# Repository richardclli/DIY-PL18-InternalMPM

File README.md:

# DIY-PL18-InternalMPM
An internal MPM (Multi-Protocol Module) for Flysky PL18 Mod

This internal module works with the modified version of Flysky PL18 that flashes with EdgeTX:

https://github.com/EdgeTX/edgetx/wiki/PL18-Hardware-Mod-for-Complete-EdgeTX-Support

For MPM firmware download, please visit the official page:

https://github.com/pascallanger/DIY-Multiprotocol-TX-Module

## Installation Procedures:
1. Add an antenna to the PL18

2. Solder the power control wire to PI.00 pin

3. Install the PCB and insert the power control pin, you may need to use a sticky tape to ensure the MPM PCB is fixed to the PL18 PCB properly.

Note:
The 100k pull up resistor for the power control pin is for testing purpose, it DO NOT NEED to be soldered as per the images shown.

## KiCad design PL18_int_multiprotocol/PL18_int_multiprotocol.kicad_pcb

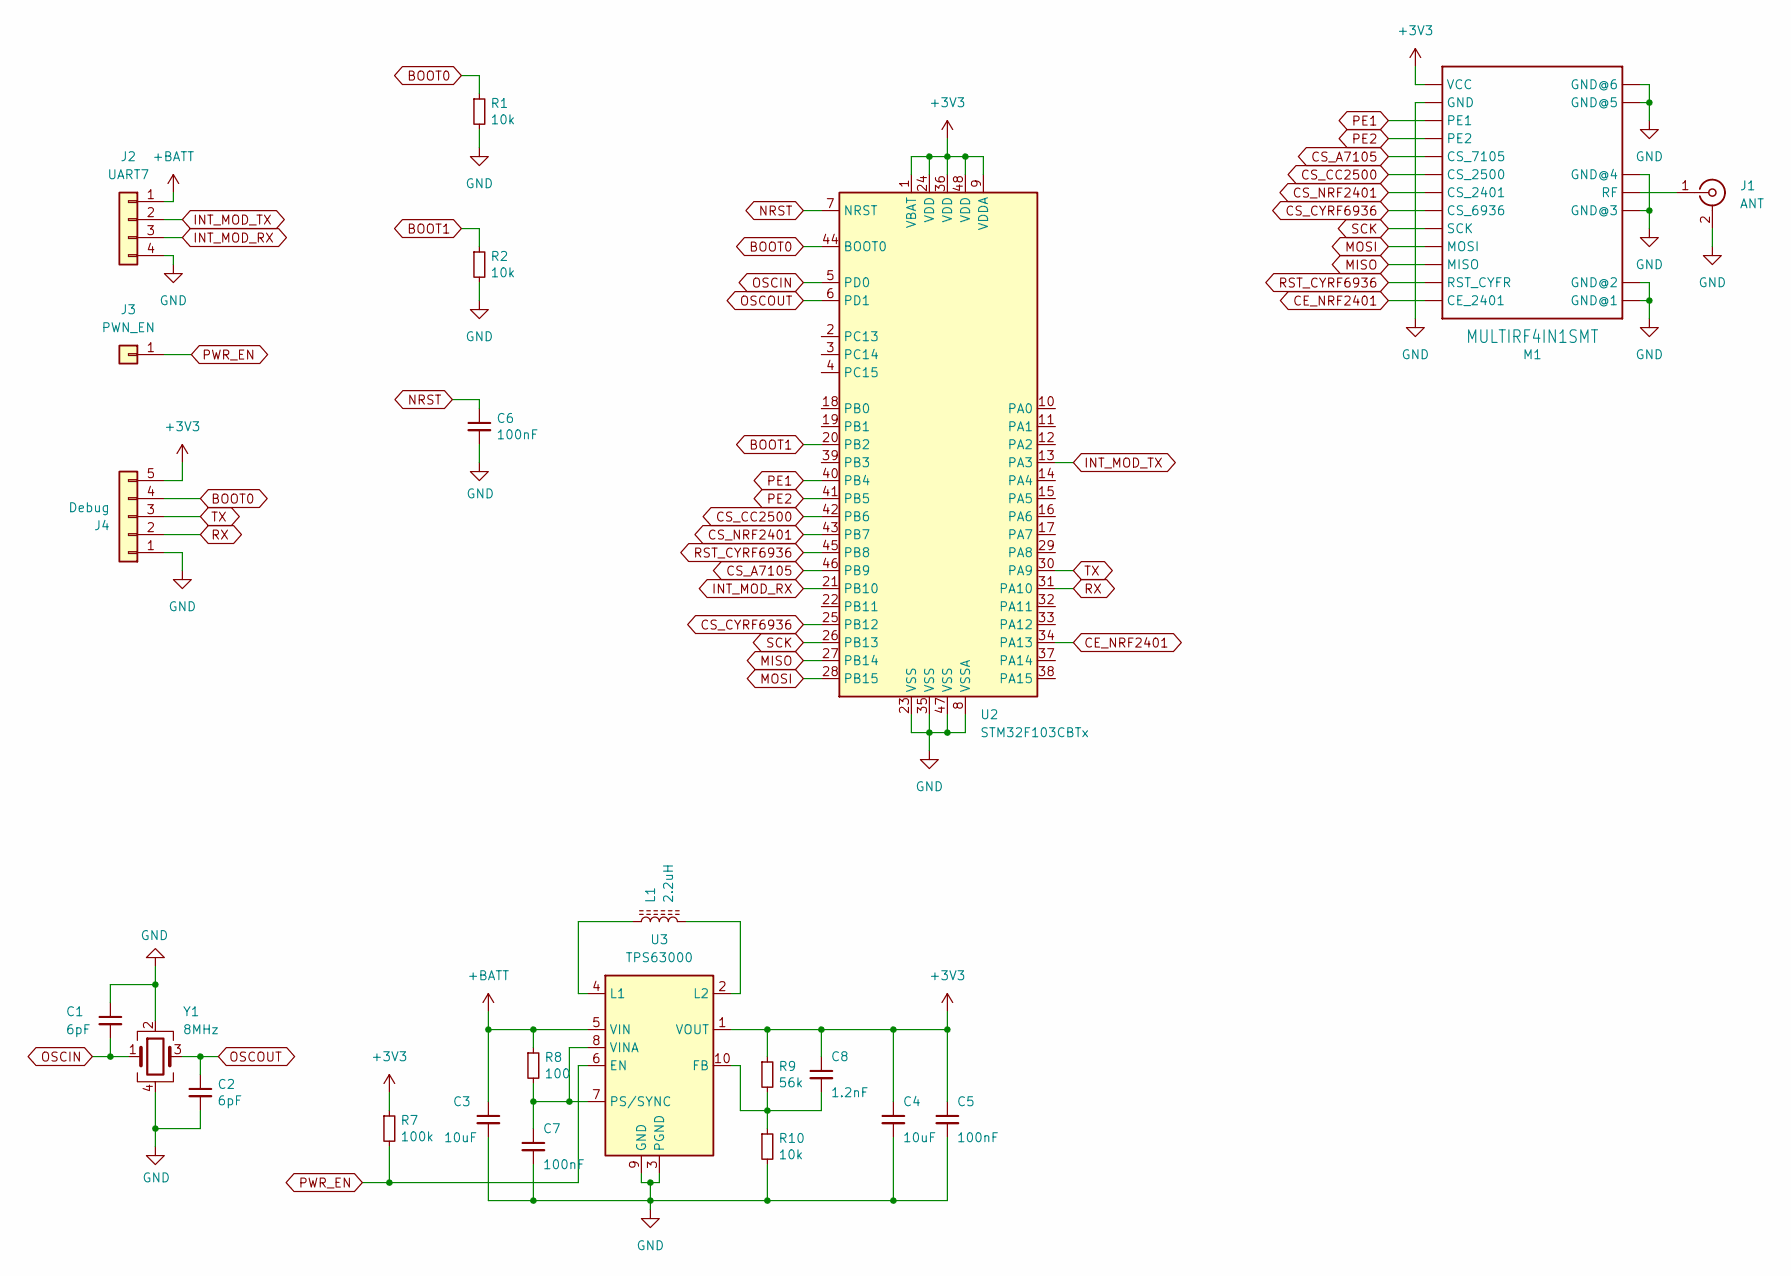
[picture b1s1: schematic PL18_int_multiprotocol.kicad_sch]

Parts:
C1, C2: 6pF; C_0603_1608Metric_Pad1.08x0.95mm_HandSolder
C3, C4: 10uF; C_0603_1608Metric_Pad1.08x0.95mm_HandSolder
C5, C6, C7: 100nF; C_0603_1608Metric_Pad1.08x0.95mm_HandSolder
C8: 1.2nF; C_0603_1608Metric_Pad1.08x0.95mm_HandSolder
J1: ANT; U.FL_Molex_MCRF_73412-0110_Vertical
J2: UART7; PinHeader_1x04_P2.54mm_Vertical_SMD_Pin1Left_Holes
J3: PWN_EN; PinHeader_1x01_P2.54mm_Horizontal
J4: Debug; JST_GH_BM05B-GHS-TBT_1x05-1MP_P1.25mm_Vertical
L1: 2.2uH; L_Abracon_ASPI-3012S
M1: MULTIRF4IN1SMT; MULTIRF4IN1-SMT
R1, R2, R10: 10k; R_0603_1608Metric_Pad0.98x0.95mm_HandSolder
R7: 100k; R_0603_1608Metric_Pad0.98x0.95mm_HandSolder
R8: 100; R_0603_1608Metric_Pad0.98x0.95mm_HandSolder
R9: 56k; R_0603_1608Metric_Pad0.98x0.95mm_HandSolder
U2: STM32F103CBTx; LQFP-48_7x7mm_P0.5mm
U3: TPS63000; Texas_DRC0010J_ThermalVias
Y1: 8MHz; Oscillator_SMD_Abracon_ASE-4Pin_3.2x2.5mm

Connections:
+3V3: C4.1, C5.1, C8.1, J4.5, M1.VCC, R7.1, R9.1, U2.1 (VBAT), U2.9 (VDDA), U2.24 (VDD), U2.36 (VDD), U2.48 (VDD), U3.1 (VOUT)
+BATT: C3.1, J2.1, R8.1, U3.5 (VIN)
BOOT0: J4.4, R1.1, U2.44 (BOOT0)
BOOT1: R2.1, U2.20 (PB2)
CE_NRF2401: M1.CE_2401, U2.34 (PA13)
CS_A7105: M1.CS_7105, U2.46 (PB9)
CS_CC2500: M1.CS_2500, U2.42 (PB6)
CS_CYRF6936: M1.CS_6936, U2.25 (PB12)
CS_NRF2401: M1.CS_2401, U2.43 (PB7)
GND: C1.1, C2.2, C3.2, C4.2, C5.2, C6.2, C7.2, J1.2 (Ext), J2.4, J4.1, M1.GND, M1.GND@1, M1.GND@2, M1.GND@3, M1.GND@4, M1.GND@5, M1.GND@6, R1.2, R2.2, R10.2, U2.8 (VSSA), U2.23 (VSS), U2.35 (VSS), U2.47 (VSS), U3.3 (PGND), U3.9 (GND), U3.11 (PGND), Y1.2, Y1.4
INT_MOD_RX: J2.3, U2.21 (PB10)
INT_MOD_TX: J2.2, U2.13 (PA3)
MISO: M1.MISO, U2.27 (PB14)
MOSI: M1.MOSI, U2.28 (PB15)
NRST: C6.1, U2.7 (NRST)
unnamed: C7.1, R8.2, U3.7 (PS/SYNC), U3.8 (VINA)
unnamed: C8.2, R9.2, R10.1, U3.10 (FB)
unnamed: J1.1 (In), M1.RF
unnamed: L1.1, U3.4 (L1)
unnamed: L1.2, U3.2 (L2)
OSCIN: C1.2, U2.5 (PD0), Y1.1
OSCOUT: C2.1, U2.6 (PD1), Y1.3
PE1: M1.PE1, U2.40 (PB4)
PE2: M1.PE2, U2.41 (PB5)
PWR_EN: J3.1, R7.2, U3.6 (EN)
RST_CYRF6936: M1.RST_CYFR, U2.45 (PB8)
RX: J4.2, U2.31 (PA10)
SCK: M1.SCK, U2.26 (PB13)
TX: J4.3, U2.30 (PA9)

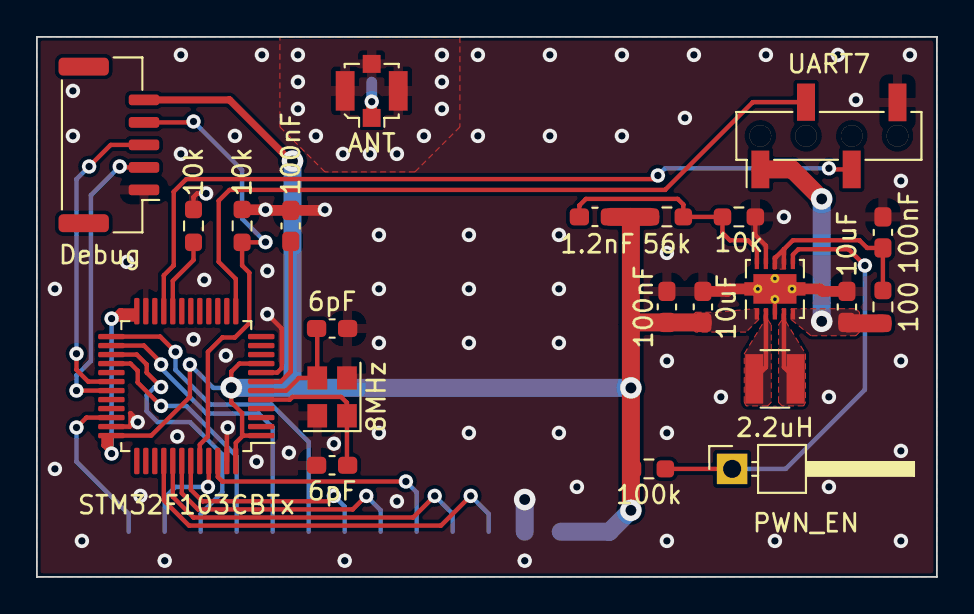
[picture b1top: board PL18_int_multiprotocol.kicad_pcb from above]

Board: 2 copper layers, 50.0 x 30.0 mm, 23 parts (1 on the bottom side), 29 nets.

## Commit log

2023-10-07 Create LICENSE
2023-10-07 Added the schematic and PCB design.
2023-10-07 Added images for documentation.
